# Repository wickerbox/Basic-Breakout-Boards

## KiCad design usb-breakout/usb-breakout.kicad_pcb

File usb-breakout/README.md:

<!--- start title --->
# USB Breakout Board vv1.1
Breadboard-compatible breakout of a micro USB connector.

Updated: 31 Dec 2016

Author: Jenner Hanni
Website: http://wickerbox.net
Company: Wickerbox Electronics
License: CERN Open Hardware License v1.2

<!--- end title --->

### Bill of Materials

<!--- bom start --->
|Ref|Qty|Description|Digikey PN|
|---|---|-----------|------|
|C1|1|CAP CER 1UF 16V X7R RADIAL|445-8614-ND|
|D1 D2|2|DIODE ZENER 3.6V 1W BZX85C3V6 DO41|BZX85C3V6-ND|
|J1|1|USB MICRO-B RECEPTACLE 5PIN SMT R/A STUDS|609-4616-1-ND|
|J2|1|HEADER MALE 5POS TH 1x05 0.1”|952-1902-ND|
|R1|1|RES 1.5K OHM 1/2W 5% CF MINI|S1.5KHCT-ND|
|R3 R2|2|RES 66.5 OHM 1/4W 1% AXIAL|66.5XBK-ND|
|SW1|1| SWITCH TACTILE SPST-NO 0.05A 24V |SW400-ND|
<!--- bom end --->

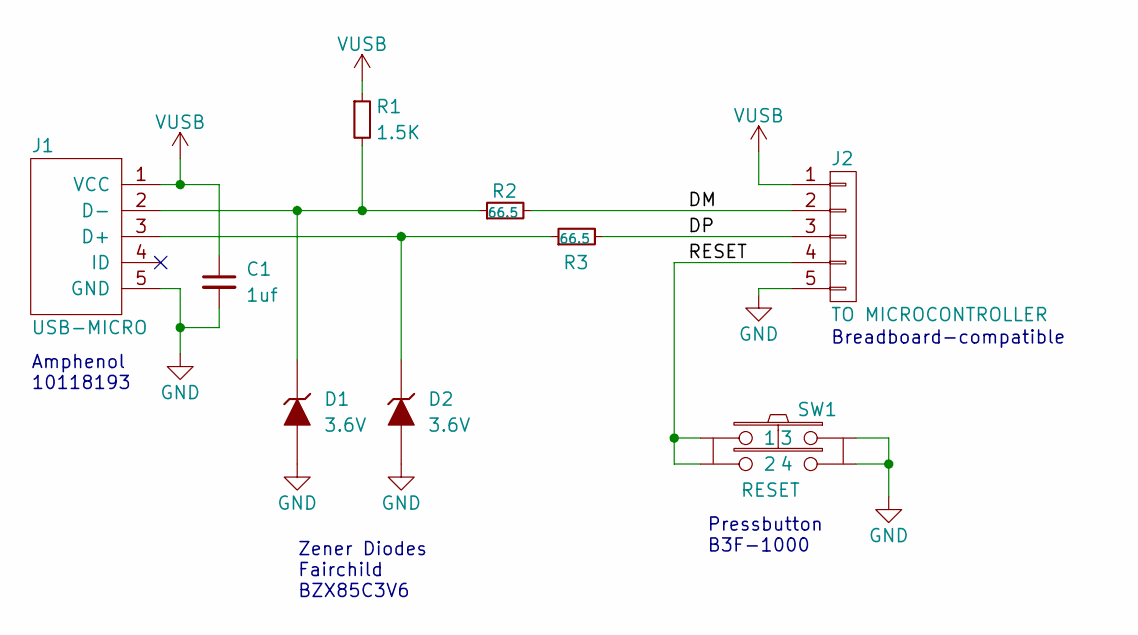
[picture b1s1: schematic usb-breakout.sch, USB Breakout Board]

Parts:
C1: 1uf; CAP-DISC-D7.5MM-P5MM
D1, D2: 3.6V; DIODE-DO-41
J1: USB-MICRO; CONN-USB-MICRO-B-AMPHENOL-10118193-0001LF
J2: TO MICROCONTROLLER; CONN-HEADER-STRAIGHT-P2.54MM-1x05
R1: 1.5K; RES-CARBONFILM-7MM
R2, R3: 66.5; RES-CARBONFILM-7MM
SW1: RESET; SWITCH-OMRON-MOMENTARY-TH-B3F-10XX

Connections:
/DM: J2.2, R2.2
/DP: J2.3, R3.2
/RESET: J2.4, SW1.1, SW1.2
GND: C1.2, D1.2 (A), D2.2 (A), J1.5 (GND), J2.5, SW1.3, SW1.4
unnamed: D1.1 (K), J1.2 (D-), R1.2, R2.1
unnamed: D2.1 (K), J1.3 (D+), R3.1
VUSB: C1.1, J1.1 (VCC), J2.1, R1.1

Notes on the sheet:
Zener Diodes Fairchild BZX85C3V6
Amphenol 10118193
Pressbutton B3F-1000
Breadboard-compatible

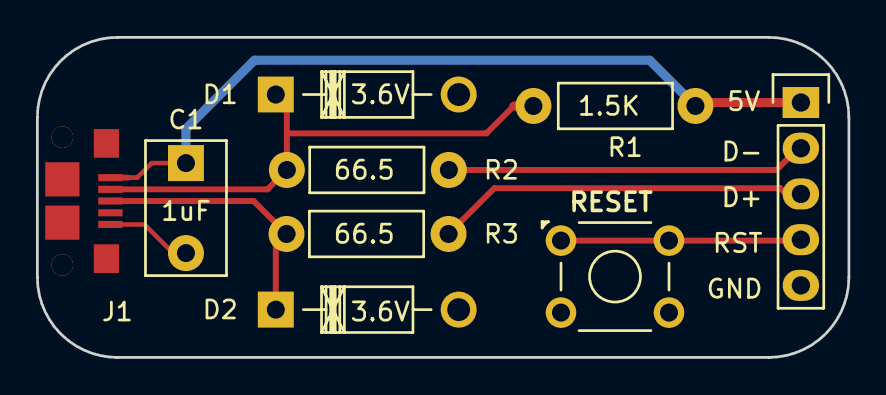
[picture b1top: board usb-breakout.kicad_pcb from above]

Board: 2 copper layers, 45.1 x 17.8 mm, 9 parts (0 on the bottom side), 7 nets.

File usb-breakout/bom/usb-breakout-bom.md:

|Ref|Qty|Description|Digikey PN|
|---|---|-----------|------|
|D1 D2|2|DIODE ZENER 3.6V 1W BZX85C3V6 DO41|BZX85C3V6-ND|
|J1|1|USB MICRO-B RECEPTACLE 5PIN SMT R/A STUDS|609-4616-1-ND|
|J2|1|HEADER MALE 5POS TH 1x05 0.1”|952-1902-ND|
|R1|1|RES 1.5K OHM 1/2W 5% CF MINI|S1.5KHCT-ND|
|R3 R2|2|RES 66.5 OHM 1/4W 1% AXIAL|66.5XBK-ND|
|SW1|1| SWITCH TACTILE SPST-NO 0.05A 24V |SW400-ND|
